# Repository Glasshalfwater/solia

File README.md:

# solia
### A compact tamagotchi in a rectangular form factor:

This originally started off as an idea for a birthday gift, however I realized that the timeline in which I had hoped to accomplish it was quite unrealistic. It also served as a fun way to learn KiCad (my previous projects were designed in EasyEDA Pro). The actual tamagotchi guided project took maybe 3-4 days to finish, but I wanted to make it, frankly, cooler. I decided to add a full-color TFT display, Kailh Choc keys for a more satisfying user experience, and a LiPO battery (of course along with temperature monitoring, fuse, etc.) for improved battery life. Soooo, it's been about a month and a half since I started this, said person's birthday passed a month ago, but hopefully it will be finally built soon. Another reason why I wanted to build something more complex than a basic tamagotchi (other than making it more interesting as a gift) was so it would be more fun to update later down the line. I could create "DLCs" or expansions to serve as further iterations or updates. (I had wanted to make a full color tamagotchi, so I was thinking of continuously adding new creatures with better graphics.)

### Images:

Wiring Schematic:

PCB Bottom Layer:

PCB Top Layer:

PCB Bottom View:

PCB Top View:

Assembly Isometric View:

Assembly Top View:

Assembly Bottom View:

Assembly Side View:

### Onshape Link:
[Onshape Document :D](https://cvilleschools.onshape.com/documents/4abba4c252e7ebcaf10d09a4/w/88913430d3dbe53bf4207c72/e/fed4882613c54d204ad1a2a2?renderMode=0&leftPanel=false&uiState=6a964f6fc21300446a4483bd) 
 
### Component List:
|Name                                                                |Quantity                                           |Price                                                                                            |Link                                                                                                                                                                                                                                                                                                                                                                                                                                                                                                                                                                                                                             |FIELD5|
|--------------------------------------------------------------------|---------------------------------------------------|-------------------------------------------------------------------------------------------------|---------------------------------------------------------------------------------------------------------------------------------------------------------------------------------------------------------------------------------------------------------------------------------------------------------------------------------------------------------------------------------------------------------------------------------------------------------------------------------------------------------------------------------------------------------------------------------------------------------------------------------|------|
|Total                                                               | N/A                                               | ~85-90 (<65 for components but + tax and shipping and depends on how expensive your shipping is)| N/A                                                                                                                                                                                                                                                                                                                                                                                                                                                                                                                                                                                                                             |      |
|PCB Boards                                                          | 5 (min quantity from JLCPCBD)                     | ~$7.00 w/ shipping                                                                              | jlcpcb.com                                                                                                                                                                                                                                                                                                                                                                                                                                                                                                                                                                                                                      |      |
|Seeed Studio XIAO ESP32 S3 Plus                                     | 1                                                 | $7.99                                                                                           | https://www.seeedstudio.com/Seeed-Studio-XIAO-ESP32S3-Plus-p-6361.html                                                                                                                                                                                                                                                                                                                                                                                                                                                                                                                                                          |      |
|Kailh Choc v2 Low Profile Keyboard Switches (brown switch variety)  | 10 (need 4 but whatever min quantity you can find)| $12.00                                                                                          | https://www.amazon.com/KAILH-Profile-Mechanical-Keyboard-Keystem/dp/B0B463YXGQ/ref=sr_1_3?crid=50VPKBCATYCO&dib=eyJ2IjoiMSJ9.Gzt2jvc4qV_Ogq9yFG0d0IUrZBKO-aG-nOpPDW2T-o3UZpg9slUbYrp-NdaWb5nNyzjzHO4fnItiBn6w3-euWRNiA3w4z6aCa8vqKvJsdxMuyc-C0Lc1-4snAM9LL09rJAOYMTBEQQNCiB7dxQz5-z2AFwkKCX9uoIKl-IvaVv-98peJEBvBUbGzvblb_yJnLZZH4Yt37W5vOiFgZcAw1gt4P6pWkpUNjcR7cHKi4VE.UwQbpqP1bqHfobgUEAuVg6W2DaMiG2_HCWwc6_qfBo8&dib_tag=se&keywords=kailh%2Bchoc%2Bv2%2Bbrown%2B20%2Bpcs&qid=1788232250&sprefix=kailh%2Bchoc%2Bv2%2Bbrown%2B20%2Bpcs%2Caps%2C105&sr=8-3&th=1                                                               |      |
|Cherry MX Style Blank Keycaps 1U (white - 18 x 18 mm)               | 10 (need 4)                                       | ~$10 (for ten)                                                                                  | https://www.amazon.com/PATIKIL-Universal-Replacement-Accessories-Mechanical/dp/B0B5KZQ9X9/ref=sr_1_7_sspa?crid=12ATOS6KH7DQS&dib=eyJ2IjoiMSJ9.-PEZO3lmrldqZH0to2R2HRwN5BKRn86UWDtIm__w3eBpasSO6ZcCaM8QUq_QC9RgCpf5S-4EZqDYFlEzHrvcDUFbGRBe5v_g-2uizBUqArkQR8r0fBgW3fjjAHnhHtVhcrmu-O6b1ETLkijcrdWsNscyHGEe1Wfe2qANjGtk2DE58KXFpQiHFqz2rpJbc1Yo6SbPw8HZisYYzNHv0vWksAsGGalZiP4I_vSb9mQW3ls.IQFXB0KRTVGAZzOyLXqZZXrNk55Y8BOvogiIjWzgNds&dib_tag=se&keywords=Cherry%2BMX%2BKeycaps%2Bblank%2B10pcs&qid=1788231734&sprefix=cherry%2Bmx%2Bkeycaps%2Bblank%2B10pcs%2Caps%2C93&sr=8-7-spons&sp_csd=d2lkZ2V0TmFtZT1zcF9tdGY&th=1        |      |
|1.8" TFT LCD Display                                                | 1                                                 | $14.99                                                                                          | https://shillehtek.com/products/shillehtek-1-8-inch-tft-lcd-display-module-dual-side-soldering?srsltid=AfmBOorBkotCfhiGtGBZEbm65gt_SpKaxWSlNMge2-bRZPlzXLDWFU5m                                                                                                                                                                                                                                                                                                                                                                                                                                                                 |      |
|3.7v 1100 mAh Lithium Polymer Battery (2pin JST-PH 2.0 mm connector)| 1                                                 | ~11                                                                                             | https://www.amazon.com/EEMB-1100mAh-Battery-Rechargeable-Connector/dp/B08FD39Y5R/ref=sr_1_2?crid=1HM1N5BQI328X&dib=eyJ2IjoiMSJ9.oCONr58BVjq1YO6zXWbcvesAbRY5XX7_4r3rtE90bLa9NNh8JLkk7cYN1TguAKXxTBEzNr4n7RTipDFYOY0kFok8PXJ_RaqFTOeM5XqBTyKpjXnFFFZxt8Qh0H_12K_YS2GvWCGQCVN4dzqZoy9_aTQPhpxRUhYv0qyvhXEqAQHsb88BeH1ER5Rh7UCn4a7LD3cZmeMf-OYr3ekDTR6lgGtYbGrbhDOIBUx1luwbbbauX_Xfu3oT-MUedajhkVTIOUYdEG-fMiS34MOOhHyMdkP5FRD-IjalL2x0GSF6ifs.e3JIIOpRqOoFrKzY6wyHervbVvqlAjrnq9Ke6bO4724&dib_tag=se&keywords=1100%2BmAh%2Bbattery%2Blipo%2B3.7v&qid=1788231984&sprefix=1100%2Bmah%2Bbattery%2Blipo%2B3.7v%2Caps%2C102&sr=8-2&th=1|      |
|Temperature Sensor                                                  | 1                                                 | $2.78                                                                                           | https://www.lcsc.com/product-detail/Temperature-Sensors_ADI_TMP36GT9Z_TMP36GT9Z_C53490.html                                                                                                                                                                                                                                                                                                                                                                                                                                                                                                                                     |      |
|Passive Piezo-Electric Buzzer                                       | 10 (min purchase amount for this specific model)  | $0.75 (for ten)                                                                                 | https://www.lcsc.com/product-detail/C49246966.html?s_z=n_q_C49246966&globalKeyword=C49246966                                                                                                                                                                                                                                                                                                                                                                                                                                                                                                                                    |      |

### Setup Instructions:
Once your PCBs, case, and components arrive (list of used components), attach the XIAO via USB-C data cable to a computer capable of flashing firmware. There are multiple ways of doing so, but given that the firmware is already a .ino file, one could simply install Arduino IDE and use the built in flashing tool (just google Arduino IDE install and docs). Afterwards, assemble the PCB components, where you will likely need a hot plate for the XIAO board. Or, if you didn't screw up like me, I highly recommend editing the PCB files to include holes underneat the XIAO battery pads, so you don't have to only use solder paste and hope (if you're editing the PCB, I also recommend swapping the placement of the buzzer and the XIAO, as I didn't realize that the pins from the buzzer would hit the SD card slot attached to the screen). There is a very specific order to which the components need not to be assembled, but essentially just solder the XIAO first and confirm that nothing is shorted (multimeter, etc.), then the buzzer and temperature sensor, then the keys, and lastly the screen (as long as the XIAO is first and the screen is left to last it should be fine). Afterwards, solder the temperature fuse in between one of the battery wires (I chose positive) and the female JST connector on the board and tape the fuse onto the battery's back (adjust the postition so it slots into the hole in the case). Once you've assembled everything onto the board, place foam around the bottom of the case except for in the cutout for the fuse, and nestle the battery in. Plug the battery into the board, place everything in and seal the top of the case, and you should be good to go!
# solia_firmware

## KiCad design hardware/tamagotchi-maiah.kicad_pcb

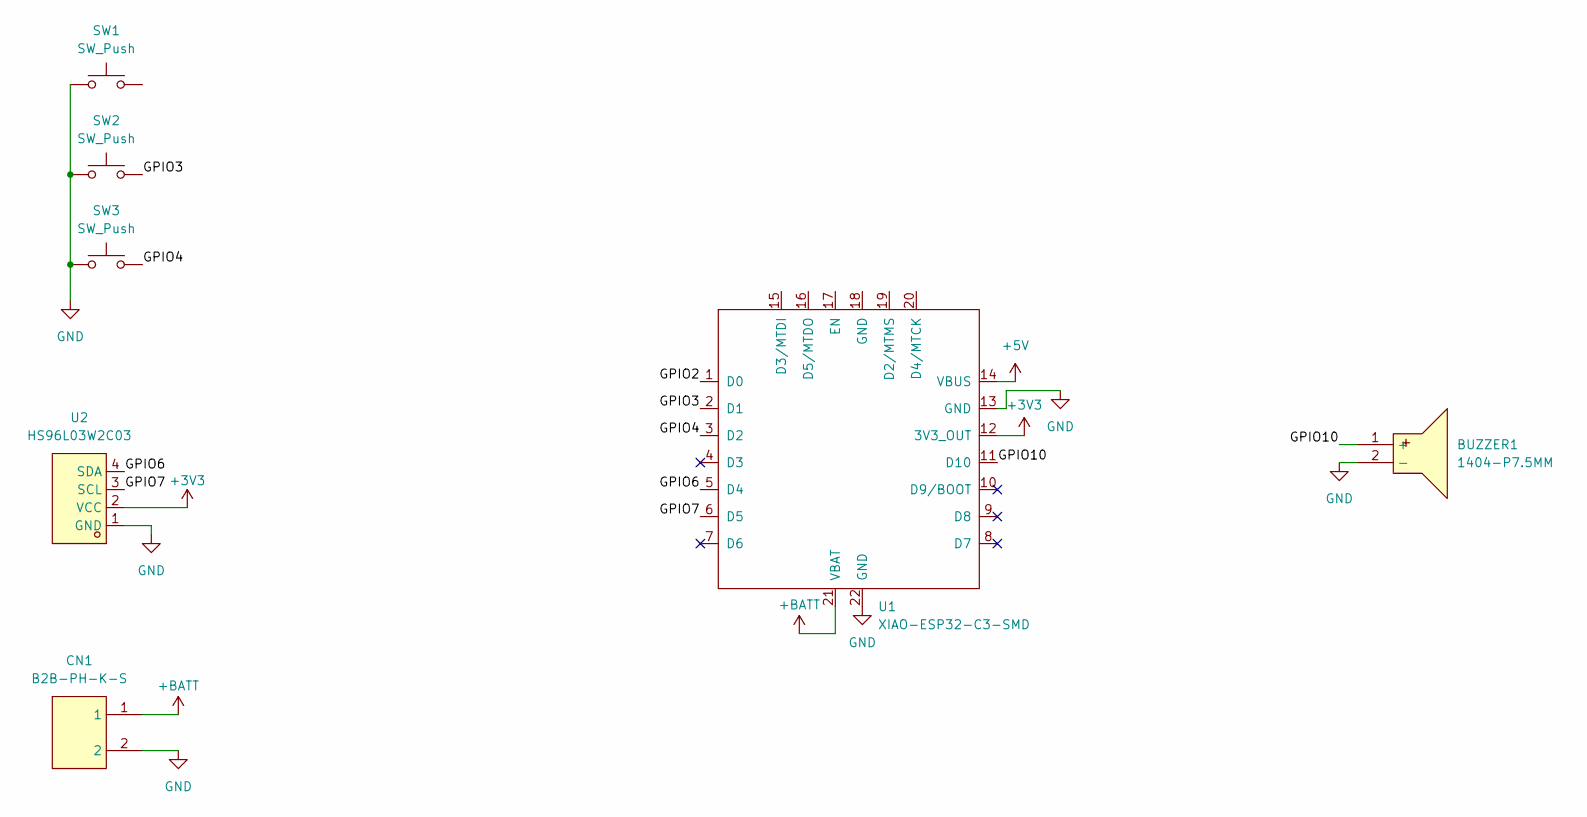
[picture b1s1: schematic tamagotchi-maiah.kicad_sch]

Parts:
BUZZER1: 1404-P7.5MM; BUZ-TH_BD14.0-P7.60-D0.8-L; MPN 1404-P7.5MM; LCSC Part C49246966
CN1: B2B-PH-K-S; CONN-TH_B2B-PH-K-S; MPN B2B-PH-K-S(LF)(SN); LCSC Part C131337
SW1, SW2, SW3: SW_Push; SW-TH_4P-L4.5-W4.5-P3.00-LS4.8
U1: XIAO-ESP32-C3-SMD
U2: HS96L03W2C03; OLED-TH_L27.8-W27.2-P2.54_C9900033791; MPN HS96L03W2C03; LCSC Part C5248080

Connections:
+3V3: U1.12 (3V3_OUT), U2.2 (VCC)
+5V: U1.14 (VBUS)
+BATT: CN1.1, U1.21 (VBAT)
/GPIO2: SW1.2, U1.1 (D0)
/GPIO3: SW2.2, U1.2 (D1)
/GPIO4: SW3.2, U1.3 (D2)
/GPIO6: U1.5 (D4), U2.4 (SDA)
/GPIO7: U1.6 (D5), U2.3 (SCL)
/GPIO10: BUZZER1.1 (+), U1.11 (D10)
GND: BUZZER1.2 (-), CN1.2, SW1.1, SW2.1, SW3.1, U1.13 (GND), U1.22 (GND), U2.1 (GND)

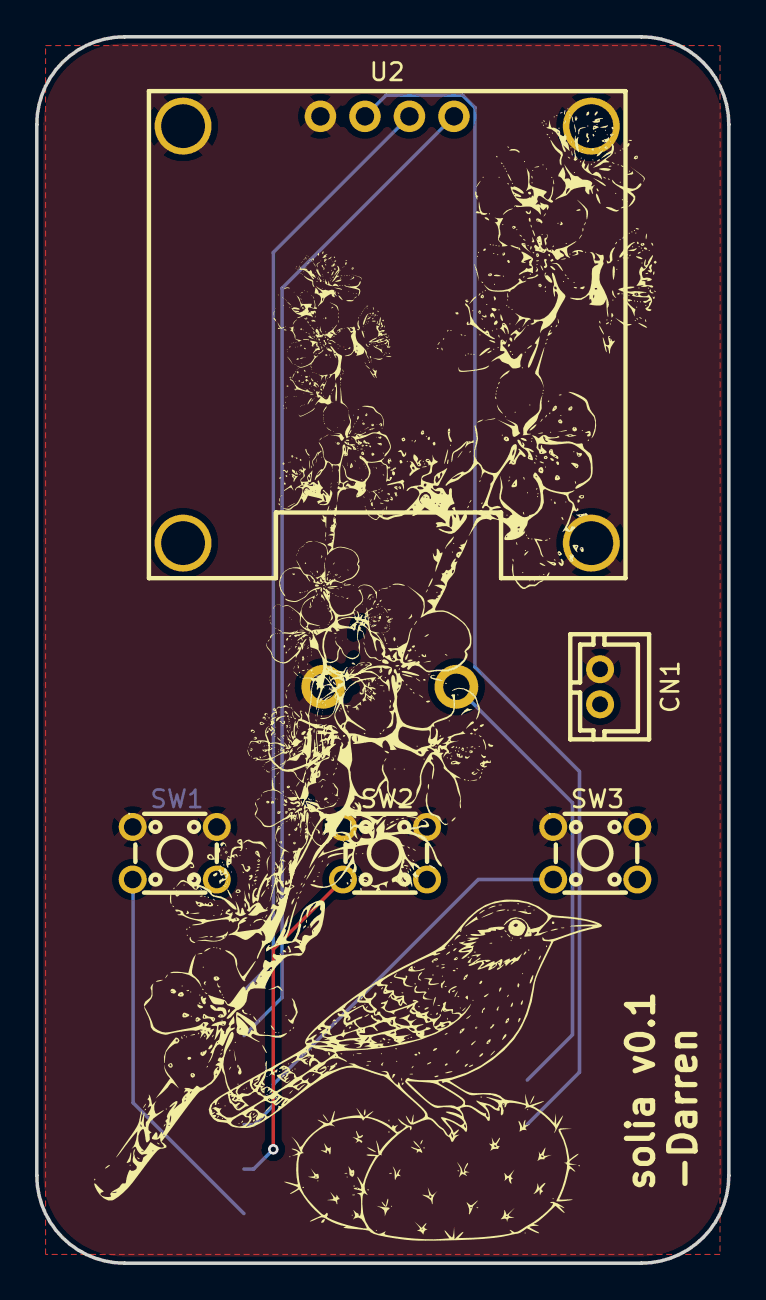
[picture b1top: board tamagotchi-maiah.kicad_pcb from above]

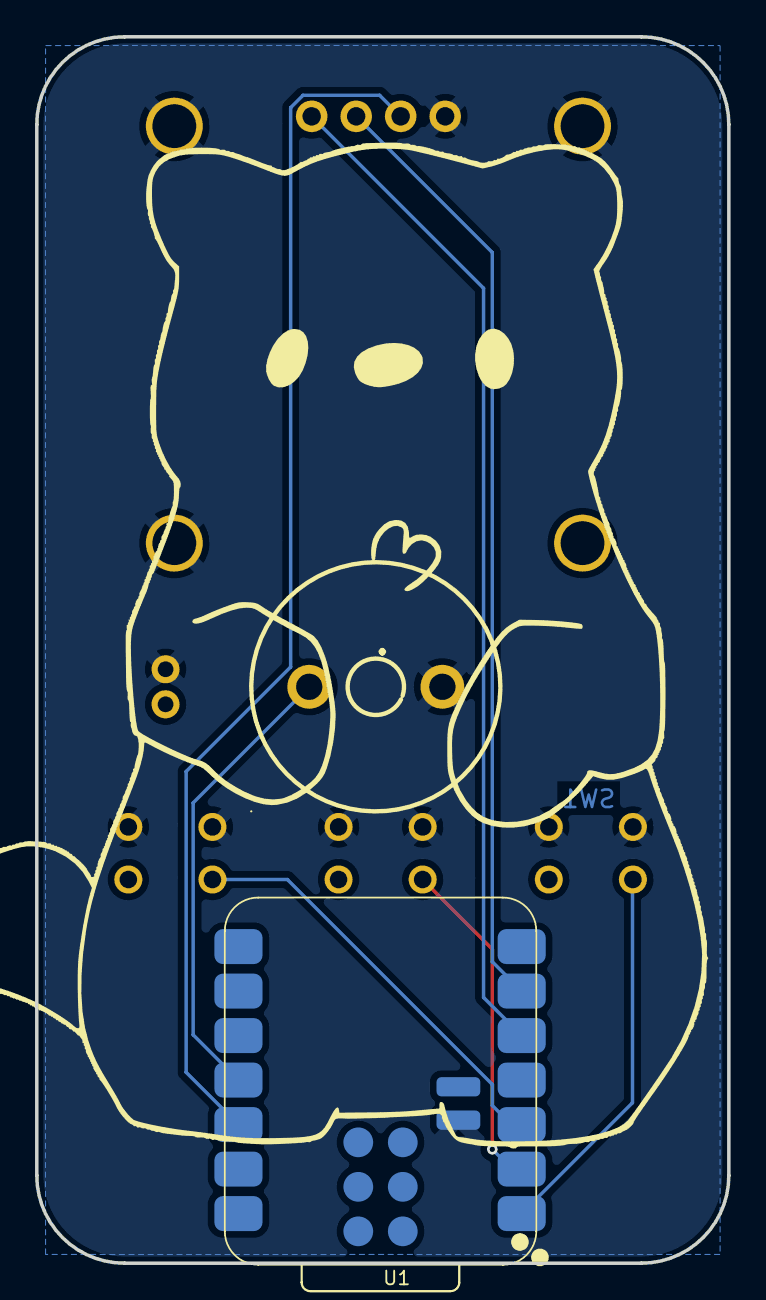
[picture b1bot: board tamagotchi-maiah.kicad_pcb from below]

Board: 2 copper layers, 39.5 x 70.0 mm, 8 parts (3 on the bottom side), 9 nets.

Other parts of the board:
.: LOGO; soup_on_silkscreen(50x58.2)
